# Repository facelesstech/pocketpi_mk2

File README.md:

# pocketpi_mk2
pocketpi_mk2

Blog post - https://facelesstech.wordpress.com/2019/05/19/pocketpi-mk2/
Youtube - https://youtu.be/y0IsOCY6VTw

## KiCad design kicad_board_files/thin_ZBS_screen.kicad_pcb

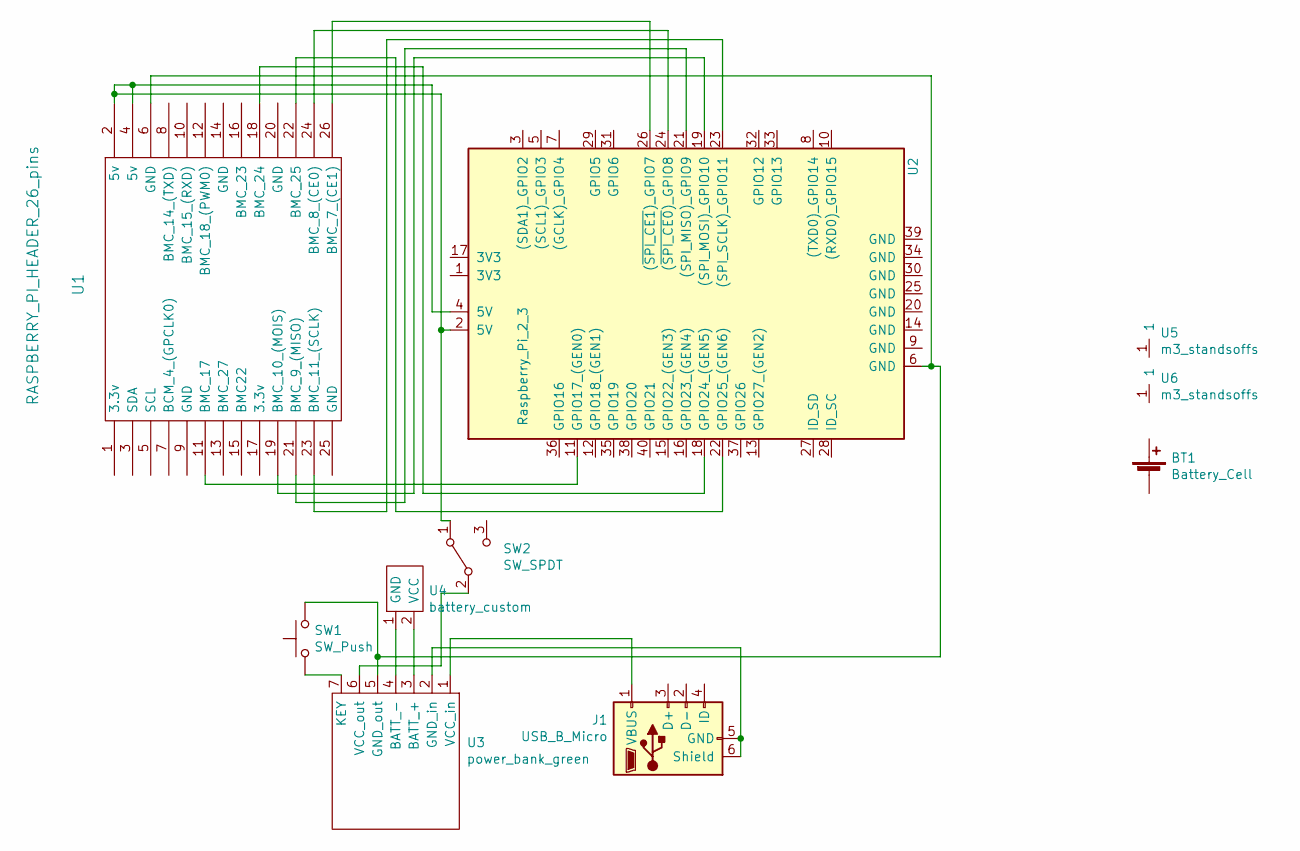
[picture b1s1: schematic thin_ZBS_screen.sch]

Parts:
BT1: Battery_Cell; 1500mha_battery_custom
J1: USB_B_Micro; USB_Micro-B_Molex-105017-0001
SW1: SW_Push; SMD_2pin_button_custom
SW2: SW_SPDT; 3_pin_switch_custom
U1: RASPBERRY_PI_HEADER_26_pins; 3.5_screen_outline
U2: Raspberry_Pi_2_3; raspberry_pi_gpio_TH_outline_w_2_holes
U3: power_bank_green
U4: battery_custom; jst_2pin_custom
U5, U6: m3_standsoffs; male_header_single

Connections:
unnamed: J1.1 (VBUS), U3.1 (VCC_in)
unnamed: J1.5 (GND), J1.6 (Shield), U3.2 (GND_in)
unnamed: SW1.1, U3.7 (KEY)
unnamed: SW1.2, U1.6 (GND), U2.6 (GND), U3.5 (GND_out)
unnamed: SW2.1 (A), U1.2 (5v), U1.4 (5v), U2.2 (5V), U2.4 (5V)
unnamed: SW2.2 (B), U3.6 (VCC_out)
unnamed: U1.11 (BMC_17), U2.11 (GPIO17_(GEN0))
unnamed: U1.18 (BMC_24), U2.18 (GPIO24_(GEN5))
unnamed: U1.19 (BMC_10_(MOIS)), U2.19 ((SPI_MOSI)_GPIO10)
unnamed: U1.21 (BMC_9_(MISO)), U2.21 ((SPI_MISO)_GPIO9)
unnamed: U1.22 (BMC_25), U2.22 (GPIO25_(GEN6))
unnamed: U1.23 (BMC_11_(SCLK)), U2.23 ((SPI_SCLK)_GPIO11)
unnamed: U1.24 (BMC_8_(CE0)), U2.24 ((~SPI_CE0~)_GPIO8)
unnamed: U1.26 (BMC_7_(CE1)), U2.26 ((~SPI_CE1~)_GPIO7)
unnamed: U3.3 (BATT_+), U4.2 (VCC)
unnamed: U3.4 (BATT_-), U4.1 (GND)

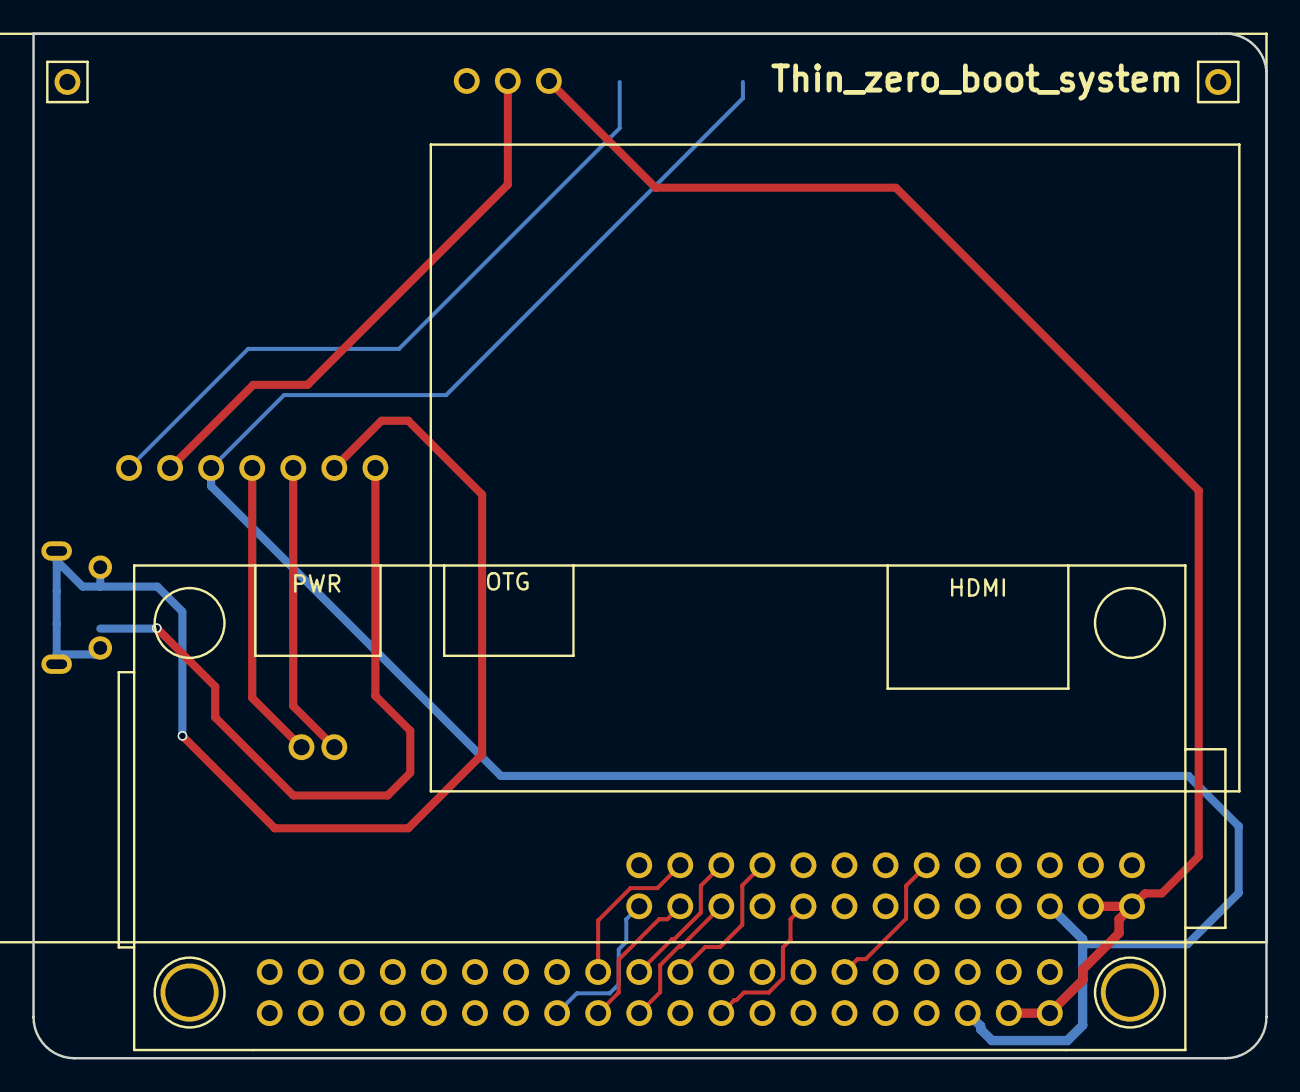
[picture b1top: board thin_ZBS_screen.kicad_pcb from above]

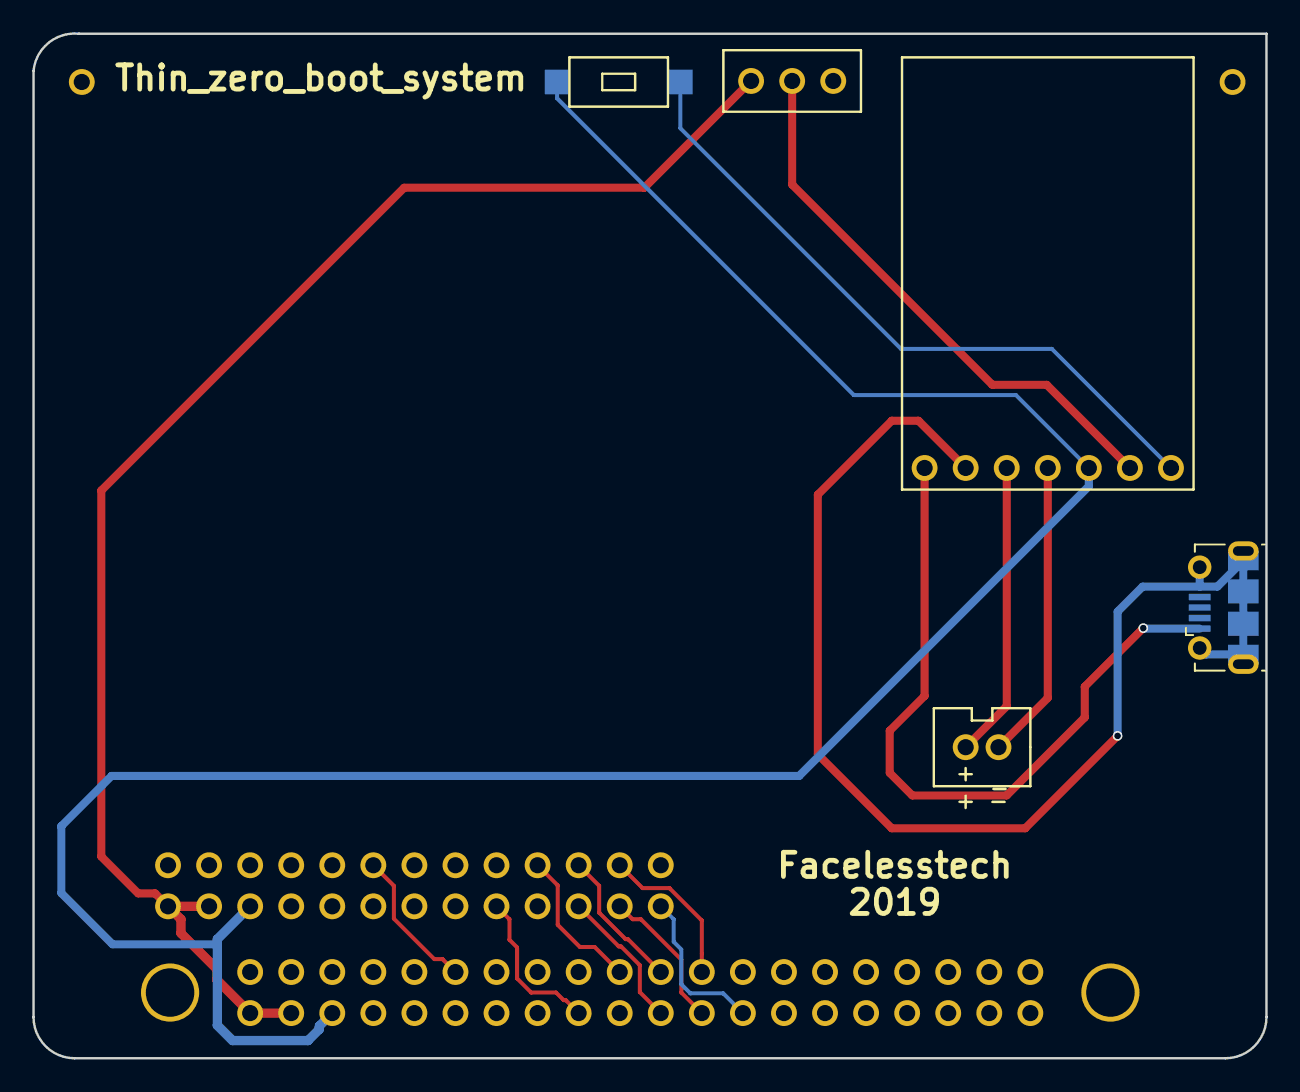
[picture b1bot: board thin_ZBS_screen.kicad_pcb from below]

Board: 2 copper layers, 76.3 x 63.4 mm, 10 parts (5 on the bottom side), 16 nets.

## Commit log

2019-05-19 board files
2020-02-27 added links to readme
